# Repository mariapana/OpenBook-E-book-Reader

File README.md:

```
        .--.                   .---.
    .---|__|           .-.     |~~~|
.--|===|--|_          |_|     |~~~|--.
|  |===|  |'\     .---!~|  .--|   |--|		   ___                   ____              _    
|%%|   |  |.'\    |===| |--|%%|   |  |		  / _ \ _ __   ___ _ __ | __ )  ___   ___ | | __
|%%|   |  |\.'\   |   | |__|  |   |  |		 | | | | '_ \ / _ \ '_ \|  _ \ / _ \ / _ \| |/ /
|  |   |  | \  \  |===| |==|  |   |  |		 | |_| | |_) |  __/ | | | |_) | (_) | (_) |   < 
|  |   |__|  \.'\ |   |_|__|  |~~~|__|		  \___/| .__/ \___|_| |_|____/ \___/ \___/|_|\_\
|  |===|--|   \.'\|===|~|--|%%|~~~|--|		       |_|                                      
^--^---'--^    `-'`---^-^--^--^---'--'
```

## Table of Contents

1. [Block Diagram](#block-diagram)
2. [Bill of Materials (BOM)](#bill-of-materials-(bom))
3. [Components. Functionality. Measurements](#components-functionality-measurements)
4. [ESP32 C6 Pin Connections](#esp32-c6-pin-connections)
5. [Design Comments]()

## Block Diagram

## Bill of Materials (BOM)

| Component | Link | Datasheet |
|-----------|-------------|-----------|
| Buttons (x3) | [Mouser](https://ro.mouser.com/ProductDetail/E-Switch/TL3315NF250Q?qs=g35H13458Kaz43%252B3owu1iQ%3D%3D) | [Datasheet](https://www.mouser.com/datasheet/2/140/TL3315-345930.pdf?srsltid=AfmBOoqCqHlNTSgC-O2LFAWm6s4LAd71f8YVI18lGMMVCCY181TTsQEw)|
| BD5229G-TR | [Digikey](https://www.digikey.ee/en/models/658502) | [Datasheet](https://fscdn.rohm.com/en/products/databook/datasheet/ic/power/voltage_detector/bd52xxg-e.pdf)|
| CPH3225A | [SnapMagic](https://www.snapeda.com/parts/CPH3225A/Seiko+Instruments/view-part/?ref=eda) | [Datasheet](https://www.snapeda.com/parts/CPH3225A/Seiko%20Instruments/datasheet/) |
| Diode | [DigiKey](https://www.digikey.com/en/products/detail/littelfuse-inc/PGB1010603MR/715755?utm_source=snapeda&utm_campaign=buynow&utm_medium=aggregator) | [Datasheet](https://www.littelfuse.com/assetdocs/pulseguard-esd-suppressors-pgb1-datasheet?assetguid=8a337998-d54d-466b-be4e-dc5bcd1f9321) |
| Display Connector | [SnapMagic](https://www.snapeda.com/parts/FH34SRJ-24S-0.5SH(99)/Hirose/view-part/) | [Datasheet](https://ro.mouser.com/datasheet/2/185/FH34SRJ_24S_0_5SH_99__CL0580_1255_6_99_2DDrawing_0-1615044.pdf)|
| Environmental Sensor BME680 | [DigiKey](https://www.digikey.com/en/products/detail/bosch-sensortec/bme680/7401317) | [Datasheet](https://www.bosch-sensortec.com/media/boschsensortec/downloads/datasheets/bst-bme680-ds001.pdf)	|
| ESP32 C6 | [Mouser](https://ro.mouser.com/ProductDetail/Espressif-Systems/ESP32-C6-WROOM-1-N8?qs=8Wlm6%252BaMh8ST02Gmwp74cw%3D%3D) | [Datasheet](https://ro.mouser.com/datasheet/2/891/Espressif_ESP32_C6_WROOM_1__Datasheet_V0_1_PRELIMI-3239987.pdf)|
| External NOR Flash (64MB) | [Mouser](https://ro.mouser.com/ProductDetail/Winbond/W25Q512JVEIQ?qs=l7cgNqFNU1jw6svr3at6tA%3D%3D) | [Datasheet](https://ro.mouser.com/datasheet/2/949/Winbond_W25Q512JV_Datasheet-3240039.pdf)|
| Led | [GrabCAD](https://grabcad.com/library/0603-smd-led-1) | [Datasheet](https://www.snapeda.com/parts/KP-1608SURCK/Kingbright/datasheet/) |
| MAX17048G+T10	| [SnapMagic](https://www.snapeda.com/parts/MAX17048G+T10/Analog+Devices/view-part/?ref=eda) | [Datasheet](https://www.snapeda.com/parts/MAX17048G+T10/Analog%20Devices/datasheet/) |
| Li-Po Battery Charging Controller | [Mouser](https://ro.mouser.com/ProductDetail/Microchip-Technology/MCP73831T-3ACI-OT?qs=yUQqVecv4quInAWkk8YFWg%3D%3D) | [Datasheet](https://ro.mouser.com/datasheet/2/268/MCP73831_Family_Data_Sheet_DS20001984H-3441711.pdf)|
| LDO Regulator | [Mouser](https://ro.mouser.com/ProductDetail/Torex-Semiconductor/XC6220A331MR-G?qs=AsjdqWjXhJ8ZSWznL1J0gg%3D%3D) | [Datasheet](https://ro.mouser.com/datasheet/2/760/xc6220-3371556.pdf)|
| N-channel MOSFET | [DigiKey](https://www.digikey.ro/ro/products/detail/vishay-siliconix/SI1308EDL-T1-GE3/4876435?s=N4IgTCBcDaIMoEkCMBmADADgKIBEAyAtACpIEDiWKIAugL5A) | [Datasheet](https://www.vishay.com/docs/63399/si1308edl.pdf)|
| P-channel MOSFET | [DigiKey](https://www.digikey.com/en/products/detail/diodes-incorporated/DMG2305UX-7/4340667) | [Datasheet](https://www.diodes.com/assets/Datasheets/DMG2305UX.pdf) |
| PFMF.050.2 | [Mouser](https://eu.mouser.com/ProductDetail/Schurter/PFMF0502?qs=1auRipcfynCums5v1iucSA%3D%3D&utm_source=findchips&utm_medium=aggregator&utm_campaign=PFMF0502&utm_term=PFMF0502&utm_content=Schurter) | [Datasheet](https://ro.mouser.com/datasheet/2/358/typ_PFMF-1275918.pdf) |
| Power Inductor | [Mouser](https://ro.mouser.com/ProductDetail/Bourns/SRR4828A-101M?qs=EU6FO9ffTwcw5i9FweW3JA%3D%3D) | [Datasheet](https://ro.mouser.com/datasheet/2/54/srr4828a-1391533.pdf)|
| Qwiic | [DigiKey](https://www.digikey.com/en/products/detail/onion-corporation/om-e-qwiic/9922970) | [Datasheet](https://cdn.sparkfun.com/assets/parts/1/2/2/8/9/Qwiic_Connector_Datasheet.pdf)|
| RCL CPOL 3528 | [DigiKey](https://www.snapeda.com/parts/TAJB475K025RNJ/AVX/view-part/?ref=dk&t=capacitor%203528&con_ref=None) | [Datasheet](https://s3.amazonaws.com/snapeda/datasheet/TAJB475K025RNJ_AVX.pdf) |
| Resistors | [Mouser](https://ro.mouser.com/c/?q=resistor%200402) | [Datasheet](https://ro.mouser.com/c/?q=resistor%200402)|
| Schottky Diodes | [Mouser](https://ro.mouser.com/ProductDetail/KYOCERA-AVX/SD0805S020S1R0?qs=jCA%252BPfw4LHbpkAoSnwrdjw%3D%3D) | [Datasheet](https://ro.mouser.com/datasheet/2/40/schottky-3165252.pdf)|
| SD Module | [Comet](https://store.comet.srl.ro/Catalogue/Product/43497/) | [Datasheet](https://store.comet.bg/download-file.php?id=8824)|
| SMC Diode | [DigiKey](https://www.digikey.ro/ro/products/detail/smc-diode-solutions/MBR0530/16692306) | [Datasheet](https://www.smc-diodes.com/propdf/MBR0530%20N0717%20REV.A.pdf)|
| Transistors | [Mouser](https://ro.mouser.com/ProductDetail/Diodes-Incorporated/DMG2305UX-7?qs=L1DZKBg7t5F%2FNBHrjfxC%252Bg%3D%3D) | [Datasheet](https://www.diodes.com/assets/Datasheets/DMG2305UX.pdf)|
| TP20R | [Mouser](https://eu.mouser.com/ProductDetail/Adafruit/3825?qs=%252bEew9%252b0nqrAn6n76%252bB5vZg%3D%3D&utm_source=findchips&utm_medium=aggregator&utm_campaign=3825&utm_term=3825&utm_content=Adafruit) | [Datasheet](https://cdn-shop.adafruit.com/product-files/3825/3825_diagram.PDF) |
| USB-C Connector | [Mouser](https://ro.mouser.com/ProductDetail/GCT/USB4110-GF-A?qs=KUoIvG%2F9IlYiZvIXQjyJeA%3D%3D) | [Datasheet](https://ro.mouser.com/datasheet/2/837/GCT_USB4110_Product_Drawing___20k_cycles-3455479.pdf)|
| USBLC6-2SC6Y | [Digikey](https://www.digikey.ro/ro/products/detail/stmicroelectronics/USBLC6-2SC6Y/2819177?s=N4IgTCBcDaIKoGUBCAZAwgNgLRgZgmiALoC%2BQA) | [Datasheet](https://www.st.com/content/ccc/resource/technical/document/datasheet/group0/94/15/6c/58/ba/91/46/42/DM00055262/files/DM00055262.pdf/jcr:content/translations/en.DM00055262.pdf)|

## Components. Functionality. Measurements

The system is built around an **ESP32 C6 microcontroller** featuring a RISC-V 32-bit architecture with integrated Wi-Fi 6 (802.11ax), Bluetooth 5 with Long Range support, and Zigbee/Thread capabilities for low-power mesh networking. Operating at 160 MHz with a 4-stage pipeline, it includes 320KB ROM, 528KB SRAM (512KB high-performance + 16KB low-power), and 30 GPIO pins. This central processor manages all communications, peripherals, and power consumption (160μA in deep sleep, 10mA active).

The visual interface is a **7.5-inch E-Paper (E-Ink) display** with 800×480 resolution, connected via SPI. This low-power display (1.2mW active, 0.1mW standby) maintains image visibility without power, making it ideal for battery-efficient applications. Key connections include MOSI, SCK, CS, DC, RST, and BUSY pins to the ESP32.

For environmental monitoring, a **BME688 multi-sensor** provides comprehensive measurements including:
- Gas detection (VOCs, CO, hydrogen)
- Humidity sensing (0-100% RH, ±3% accuracy)
- Temperature monitoring (-40°C to 85°C, ±0.5°C accuracy)
- Pressure detection (300-1100 hPa, ±0.6 hPa accuracy)

This I2C-connected sensor consumes approximately 3.6mA during measurements and just 0.1μA in sleep mode.

Power is supplied by a **3.7V 1800-2500mAh LiPo battery** (CELLEVIA LP584174) with USB-C charging capability. The system employs an **MCP73831T charging controller** for efficient battery management including precharge/fast charge modes, thermal regulation, and overvoltage protection. A dedicated **LDO voltage regulator** stabilizes the 3.3V supply for components, while a **voltage supervisor** monitors power levels and handles system resets when necessary.

The device features multiple storage options:
- **MicroSD card slot** (up to 32GB, FAT32) for e-books and user data, connected via SPI
- **64MB External NOR Flash** for firmware and critical system data
- **DS3231 RTC module** provides accurate timekeeping even during power loss, with battery backup and I2C connectivity

User input is facilitated through **three tactile push buttons** connected to GPIO pins for navigation and control functions. An **I2C-based QWIIC/Stemma QT connector** enables easy integration of additional modules and sensors.

The board includes comprehensive connectivity through:
- USB-C connector with ESD protection (PFMF varistor) and reverse polarity protection (Schottky barrier diode)
- Wi-Fi 6 and Bluetooth 5 wireless capabilities
- Various test pads for debugging and development

## ESP32 C6 Pin Connections

| Pin/Port    | Connected To             | Description                                       |
|-------------|--------------------------|---------------------------------------------------|
| EN          | RESET Button             | Hardware reset button                             |
| IO0         | INT_RTC                  | Interrupt signal from RTC                         |
| IO1         | 32KHz                    | 32kHz clock signal input                          |
| IO2         | MISO                     | Master In Slave Out for SPI devices               |
| IO3         | EPD_BUSY                 | E-Ink display busy status indicator               |
| IO4         | SS_SD                    | Chip select for SD card                           |
| IO5         | EPD_DC                   | Data/Command control for E-Ink display            |
| IO6         | SCK                      | SPI clock signal                                  |
| IO7         | MOSI                     | Master Out Slave In for SPI devices               |
| IO8         | 3V3                      | 3.3V power supply                                 |
| IO9         | BOOT Button              | Boot mode selection button                        |
| IO10        | EPD_CS                   | Chip select for E-Ink display                     |
| IO11        | FLASH_CS                 | Chip select for external Flash memory             |
| IO12        | USB_D-                   | USB data negative                                 |
| IO13        | USB_D+                   | USB data positive                                 |
| IO15        | CHANGE Button            | User action button                                |
| IO16/TXD0   | TX (UART)                | UART transmit line                                |
| IO17/RXD0   | RX (UART)                | UART receive line                                 |
| IO18        | RTC_RST                  | Reset line for RTC module                         |
| IO19        | I2C_PW                   | Power control for I2C devices                     |
| IO20        | EPD_3V3_C                | 3.3V power for E-Ink display                      |
| IO21        | SDA                      | I2C data line (BME688, DS3231, MAX17048)          |
| IO22        | SCL                      | I2C clock line (BME688, DS3231, MAX17048)         |
| IO23        | EPD_RST                  | Reset line for E-Ink display                      |
| 3V3         | Power Rail               | 3.3V power distribution                           |
| GND         | Ground                   | Common ground connection                          |

## Design Comments

While DRC throws two Board Outline Clearance errors, I have decided to keep the position of the J2 USB C Connector as is.
This is so that the component reaches the margin of the ebook reader and can be used by the client.

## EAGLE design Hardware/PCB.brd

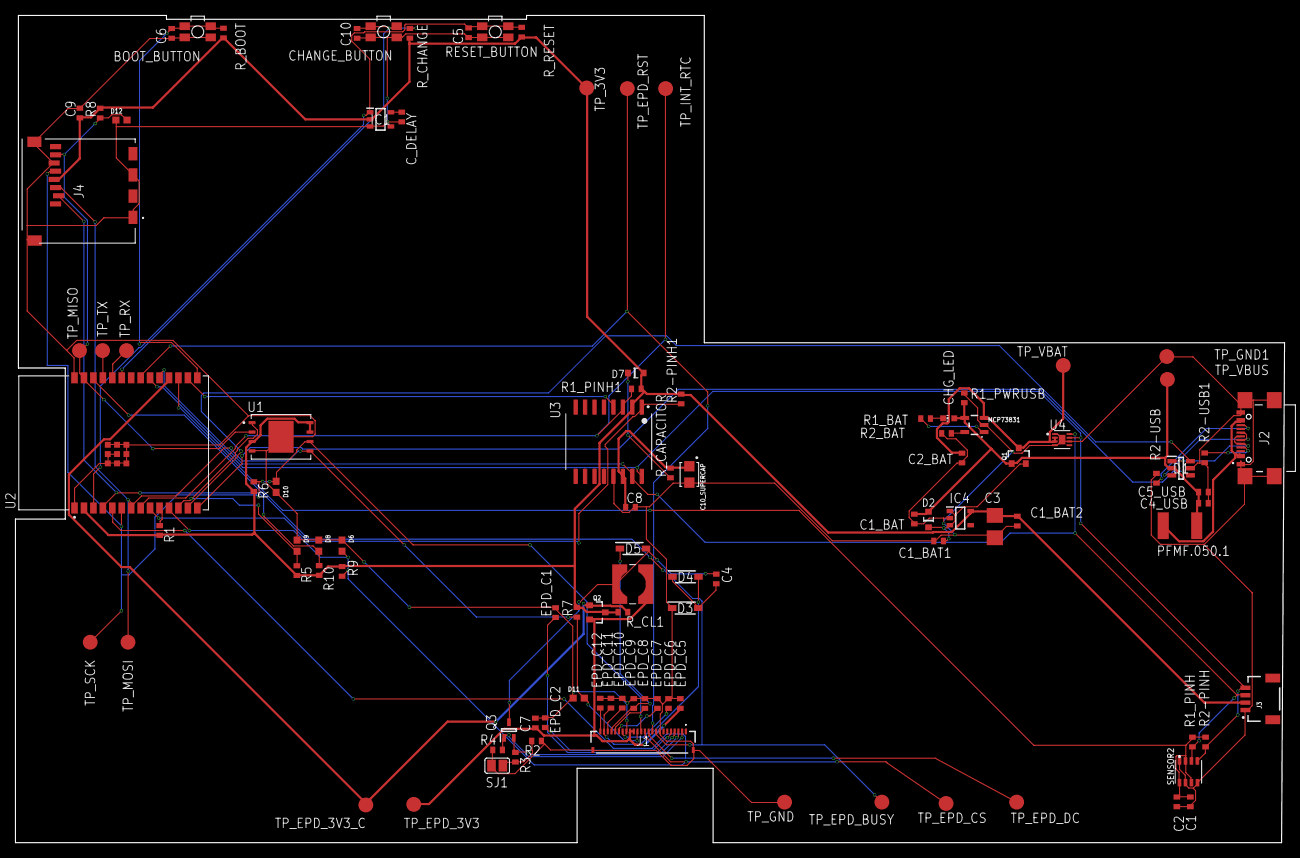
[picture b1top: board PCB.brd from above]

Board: 2 copper layers, 170.6 x 111.2 mm, 103 parts (0 on the bottom side), 55 nets.

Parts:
BOOT_BUTTON: BUTTON_CUSYOMV1; MYBUTTON
C1, C2, C4_USB, C6, C8, C9, C10: 100nF; EAGLE-LTSPICE_C0402
C1_BAT, C1_BAT1, C1_BAT2, C2_BAT, C5_USB: 4.7uF; EAGLE-LTSPICE_C0402
C3: 100uF TANT; RCL_CT3528
C4: 4.7uF/25V; EAGLE-LTSPICE_C0402
C5: 1uF; EAGLE-LTSPICE_C0402
C7: 10uF; EAGLE-LTSPICE_C0402
C10_SUPERCAP: CPH3225A; CAPCP3225X100N
CHANGE_BUTTON: BUTTON_CUSYOMV1; MYBUTTON
CHG_LED: ADAFRUIT_CHIP-LED0603
C_DELAY: 100nF; EAGLE-LTSPICE_C0402
D1: USBLC6-2SC6Y; SOT95P280X145-6N
D2: SD0805S020S1R0; ESP32_WROVER_AVX---SD0805S020S1R0_AVX_SD0805S020S1R0_0
D3, D4, D5: MBR0530; SOD3716X135N
D6, D8, D9, D10, D11, D12: PGB1010603MR; DIOC1608X36N
D7: ESP32_WROVER_AVX---SD0805S020S1R0_AVX_SD0805S020S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; ESP32_WROVER_AVX---SD0805S020S1R0_AVX_SD0805S020S1R0_0
EPD_C1, EPD_C2, EPD_C5, EPD_C6, EPD_C7, EPD_C8, EPD_C9, EPD_C10, EPD_C11, EPD_C12: 1uF/50V; EAGLE-LTSPICE_C0402
IC1: BD5229G-TR; SOT95P280X125-5N
IC4: XC6220A331MR-G; SOT95P280X120-5N
J1: FH34SRJ-24S-0.5SH_99_; FH34SRJ24S05SH99
J2: SAMACSYS_PARTS_USB4110-GF-A; SAMACSYS_PARTS_USB4110GFA
J3: QWIIC_RIGHT_ANGLE; JST04_1MM_RA
J4: 112A-TAAR-R03_ATTEND; 112ATAARR03ATTEND
L1: 68uH; IND_4828-WE-TPC_WRE
MCP73831: ESP32_WROVER_SPARKFUN-IC-POWER_MCP73831; ESP32_WROVER_SPARKFUN-IC-POWER_SOT23-5
PFMF.050.1: ESP32C6_VARISTOR_CT/CN1812
Q1, Q2: 20V/4.2A/52mΩ/1.4W; ESP32_WROVER_SPARKFUN-DISCRETESEMI_SOT23-3
Q3: SI1308EDL-T1-GE3; SOT65P210X110-3N
R1, R1_PINH, R1_PINH1, R2-PINH, R2-PINH1, R4, R5, R6, R7, R8, R9, R10: 10K; ESP32_WROVER_EAGLE-LTSPICE_R0402
R1_BAT: 200; ESP32_WROVER_EAGLE-LTSPICE_R0402
R1_PWRUSB: 100k; ESP32_WROVER_EAGLE-LTSPICE_R0402
R2: 2.2; ESP32_WROVER_EAGLE-LTSPICE_R0402
R2-USB, R2-USB1: 5k1; ESP32_WROVER_EAGLE-LTSPICE_R0402
R2_BAT: 2K; ESP32_WROVER_EAGLE-LTSPICE_R0402
R3: 0.47; ESP32_WROVER_EAGLE-LTSPICE_R0402
RESET_BUTTON: BUTTON_CUSYOMV1; MYBUTTON
R_BOOT: 10K; ESP32_WROVER_EAGLE-LTSPICE_R0402
R_CAPACITOR: 15; ESP32_WROVER_EAGLE-LTSPICE_R0402
R_CHANGE: 10K; ESP32_WROVER_EAGLE-LTSPICE_R0402
R_CL1: 10K; ESP32_WROVER_EAGLE-LTSPICE_R0402
R_RESET: 10K; ESP32_WROVER_EAGLE-LTSPICE_R0402
SENSOR2: ESP32_WROVER_BME680_BME680; ESP32_WROVER_BME680_PSON80P300X300X100-8N
SJ1: SJ
TP_3V3: TPTP20R; TP20R
TP_EPD_3V3, TP_EPD_3V3_C: TPTP20R; TP20R
TP_EPD_BUSY: TPTP20R; TP20R
TP_EPD_CS: TPTP20R; TP20R
TP_EPD_DC: TPTP20R; TP20R
TP_EPD_RST: TPTP20R; TP20R
TP_GND, TP_GND1: TPTP20R; TP20R
TP_INT_RTC: TPTP20R; TP20R
TP_MISO: TPTP20R; TP20R
TP_MOSI: TPTP20R; TP20R
TP_RX: TPTP20R; TP20R
TP_SCK: TPTP20R; TP20R
TP_TX: TPTP20R; TP20R
TP_VBAT: TPTP20R; TP20R
TP_VBUS: TPTP20R; TP20R
U1: W25Q512JVEIQ; SON127P600X800X80-9N
U2: ESP32-C6-WROOM-1-N8; XCVR_ESP32-C6-WROOM-1-N8
U3: DS3231SN#; SOIC127P1032X265-16N
U4: MAX17048G+T10; SON50P200X200X80-9N

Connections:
3V3: C1_BAT2.1, C3.+, C9.1, D7.2, IC1.2, IC4.5, J3.2, J4.P4, Q2.3, R1.2, R1_PINH1.2, R2-PINH1.2, R5.2, R6.2, R7.2, R8.2, R9.2, R10.2, R_BOOT.2, R_CHANGE.2, R_CL1.2, R_RESET.2, TP_3V3.TP, U1.3, U1.7, U1.8, U2.2, U3.2
32KHZ: R2-PINH1.1, U2.9, U3.1
DN: D1.1, J2.A7, J2.B7
DP: D1.3, J2.A6, J2.B6
EPD_3V3: C7.1, EPD_C5.1, J1.15, J1.16, L1.2, Q2.2, TP_EPD_3V3.TP
EPD_3V3_C: Q2.1, R_CL1.1, TP_EPD_3V3_C.TP, U2.18
EPD_BUSY: J1.9, TP_EPD_BUSY.TP, U2.26
EPD_CS: D6.2, J1.12, R9.1, TP_EPD_CS.TP, U2.11
EPD_DC: J1.11, TP_EPD_DC.TP, U2.5
EPD_RST: J1.10, TP_EPD_RST.TP, U2.21
FLASH_CS: D9.2, R5.1, U1.1, U2.12
GDR: J1.2, Q3.1, R4.2
GND: BOOT_BUTTON.1, BOOT_BUTTON.2, C1.2, C1_BAT.2, C1_BAT1.2, C1_BAT2.2, C2.2, C2_BAT.2, C3.-, C4_USB.2, C5.2, C5_USB.2, C6.2, C7.2, C8.2, C9.2, C10.2, C10_SUPERCAP.2, CHANGE_BUTTON.1, CHANGE_BUTTON.2, C_DELAY.2, D1.5, D3.1, D6.1, D8.1, D9.1, D10.1, D11.1, D12.1, EPD_C1.2, EPD_C2.2, EPD_C5.2, EPD_C6.2, EPD_C7.2, EPD_C8.2, EPD_C9.2, EPD_C10.2, EPD_C11.2, EPD_C12.2, IC1.3, IC4.2, J1.8, J1.17, J1.MP1, J1.MP2, J2.A1, J2.A12, J2.B1, J2.B12, J2.MP1, J2.MP2, J2.MP3, J2.MP4, J3.1, J4.G1, J4.G2, J4.G3, J4.G4, J4.P6, MCP73831.2, R1_PWRUSB.1, R2.1, R2-USB.2, R2-USB1.1, R2_BAT.1, R4.1, RESET_BUTTON.1, RESET_BUTTON.2, SENSOR2.1, SENSOR2.5, SENSOR2.7, SJ1.1, TP_GND.TP, TP_GND1.TP, U1.4, U1.9, U2.1, U2.28, U2.29_1, U2.29_2, U2.29_3, U2.29_4, U2.29_5, U2.29_6, U2.29_7, U2.29_8, U2.29_9, U3.13, U4.1, U4.4, U4.6, U4.9
GPIO8: R1.1, U2.10
I2C_PW: C1.1, C2.1, R1_PINH.2, R2-PINH.2, SENSOR2.2, SENSOR2.6, SENSOR2.8, U2.17
INT_RTC: R1_PINH1.1, TP_INT_RTC.TP, U2.8, U3.3
IO/BOOT: BOOT_BUTTON.3, BOOT_BUTTON.4, C6.1, R_BOOT.1, U2.15
IO/CHANGE: C10.1, CHANGE_BUTTON.3, CHANGE_BUTTON.4, R_CHANGE.1, U2.23
MISO: D12.2, J4.P7, R8.1, TP_MISO.TP, U1.2, U2.27
MOSI: D11.2, J1.14, J4.P3, R7.1, TP_MOSI.TP, U1.5, U2.7
unnamed: J2.A5, R2-USB1.2
unnamed: J2.B5, R2-USB.1
unnamed: C1_BAT1.1, D2.1, IC4.1, IC4.3, Q1.2
unnamed: C4.1, D3.2, D4.1
unnamed: EPD_C12.1, J1.24
unnamed: CHG_LED.C, R1_BAT.1
unnamed: MCP73831.1, R1_BAT.2
unnamed: MCP73831.5, R2_BAT.2
unnamed: C_DELAY.1, IC1.5
unnamed: EPD_C10.1, J1.22
unnamed: D7.1, R_CAPACITOR.1
unnamed: EPD_C8.1, J1.20
unnamed: EPD_C7.1, J1.19
unnamed: EPD_C6.1, J1.18
unnamed: EPD_C1.1, J1.4
unnamed: EPD_C2.1, J1.5
PREVGH: D5.1, EPD_C9.1, J1.21
PREVGL: D4.2, EPD_C11.1, J1.23
RESE: J1.3, Q3.2, R3.2
RESE': R2.2, R3.1, SJ1.2
RESET: C5.1, IC1.1, RESET_BUTTON.3, RESET_BUTTON.4, R_RESET.1, U2.3
RTC_RST: U2.16, U3.4
RX: TP_RX.TP, U2.24
SCK: D10.2, J1.13, J4.P5, R6.1, TP_SCK.TP, U1.6, U2.6
SCL: J3.4, R2-PINH.1, SENSOR2.4, U2.20, U3.16, U4.7
SDA: J3.3, R1_PINH.1, SENSOR2.3, U2.19, U3.15, U4.8
SRC: C4.2, D5.2, L1.1, Q3.3
SS_SD: D8.2, J4.P2, R10.1, U2.4
TX: TP_TX.TP, U2.25
USB_D+: D1.4, U2.14
USB_D-: D1.6, U2.13
VBAT: C2_BAT.1, MCP73831.3, Q1.3, TP_VBAT.TP, U4.2, U4.3
VBUS: C1_BAT.1, C4_USB.1, C5_USB.1, CHG_LED.A, D1.2, D2.2, MCP73831.4, PFMF.050.1.2, Q1.1, R1_PWRUSB.2, TP_VBUS.TP
VRTC: C8.1, C10_SUPERCAP.1, R_CAPACITOR.2, U3.14
VUSB: J2.A4, J2.A9, J2.B4, J2.B9, PFMF.050.1.1

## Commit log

2025-04-06 Commit HW
2025-04-06 Add Manufacturing/
2025-04-14 Fix #16
2025-04-14 Fix #2
2025-04-14 Fix #12
2025-04-14 Fix #13
2025-04-14 Fix #3, Fix #4
2025-04-15 Fix #5, Fix #11
2025-04-15 Fix #14
2025-04-15 Fix #15
2025-04-16 Add full product model
2025-04-16 Add rendered PCB image
2025-04-16 Add rendered Battery image
2025-04-16 Add rendered image

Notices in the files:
parts and their libraries:
COPYRIGHT: Copyright (C) 2024 Ultra Librarian. All rights reserved.
